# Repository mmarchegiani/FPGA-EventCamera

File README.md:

# FPGA-EventCamera
In the present work, a simplified model of an event camera is implemented, featuring a 3 $\times$ 3 matrix of photodiodes that are read out from a 12-channel ADC multiplexer in synchronous mode.

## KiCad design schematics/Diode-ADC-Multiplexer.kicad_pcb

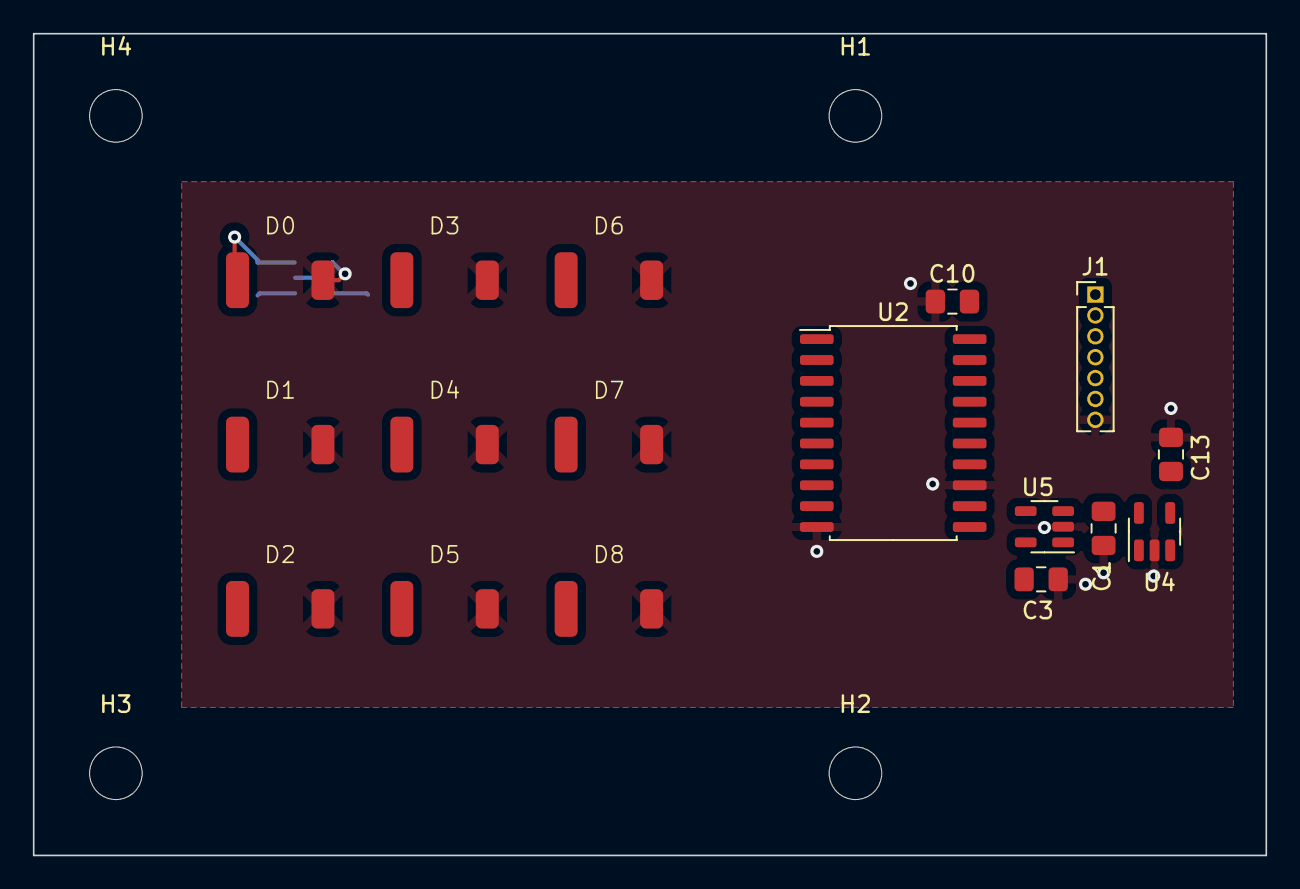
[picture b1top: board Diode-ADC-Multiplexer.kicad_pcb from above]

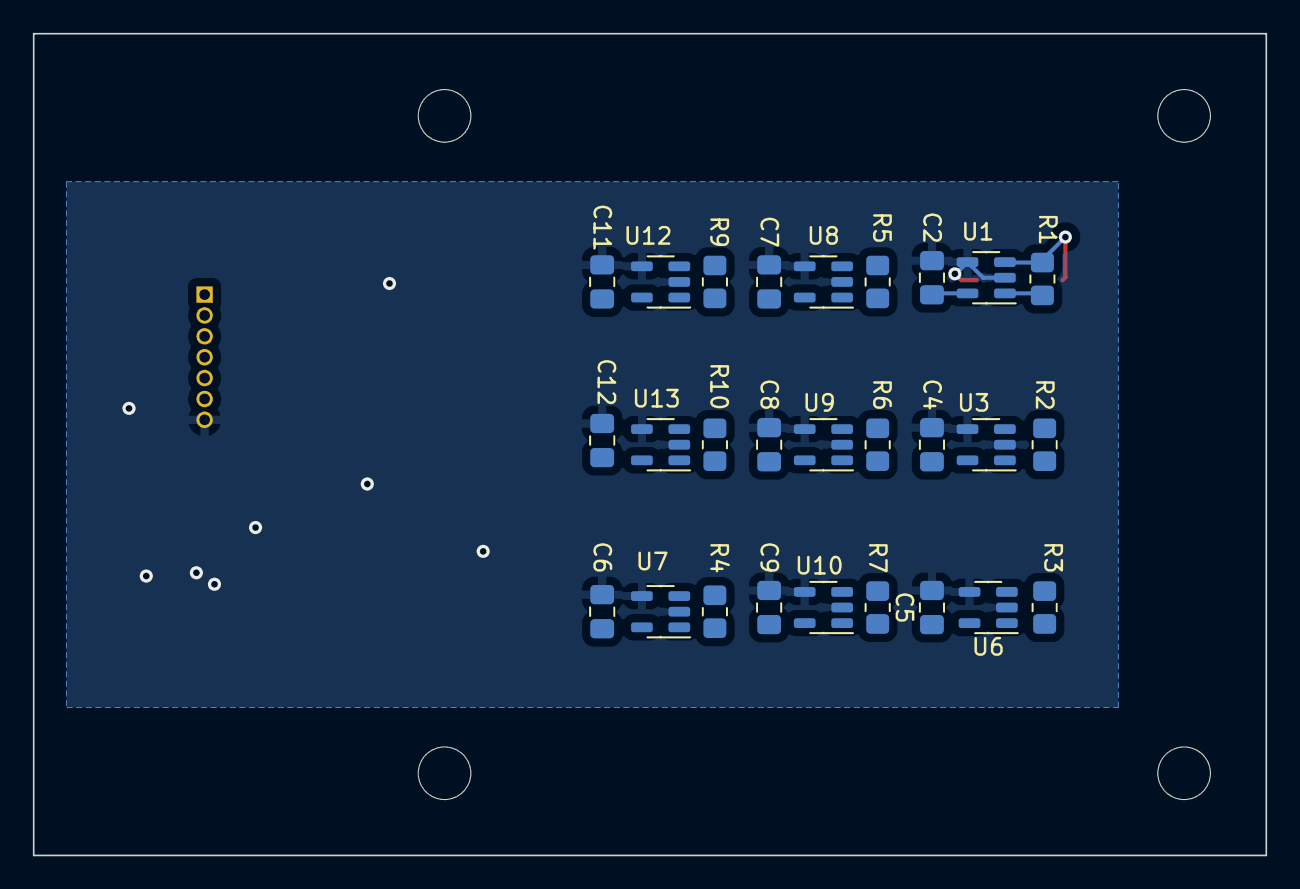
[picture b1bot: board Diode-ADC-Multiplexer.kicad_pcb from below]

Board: 2 copper layers, 75.0 x 50.0 mm, 48 parts (27 on the bottom side), 27 nets.

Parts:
C1: 22n; C_0805_2012Metric_Pad1.18x1.45mm_HandSolder
C2, C3, C4, C5, C6, C7, C8, C9, C10, C11, C12, C13: 100n; C_0805_2012Metric_Pad1.18x1.45mm_HandSolder
D0, D1, D2, D3, D4, D5, D6, D7, D8: SFH2240A01; Osram_SFH2240
H1, H2, H3, H4: MountingHole; MountingHole_3.2mm_M3
J1: To/From FPGA; PinHeader_1x07_P1.27mm_Vertical
R1, R2, R3, R4, R5, R6, R7, R9, R10: R; R_0805_2012Metric_Pad1.20x1.40mm_HandSolder
U1, U3, U5, U6, U7, U8, U9, U10, U12, U13: MCP601; SOT-23-5
U2: TLV2553; SOIC-20W_7.5x12.8mm_P1.27mm
U4: LM4120IM5-2.5; SOT-23-5

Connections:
+3.3V: C2.1, C3.1, C4.1, C5.1, C6.1, C7.1, C8.1, C9.1, C10.2, C11.1, C12.1, C13.1, J1.1, U1.5 (V+), U2.20 (VCC), U3.5 (V+), U4.3 (EN), U4.4 (VIN), U5.5 (V+), U6.5 (V+), U7.5 (V+), U8.5 (V+), U9.5 (V+), U10.5 (V+), U12.5 (V+), U13.5 (V+)
DATA_IN: J1.4, U2.17 (DATA_IN)
DATA_OUT: J1.3, U2.16 (DATA_OUT)
Diode_0: R1.2, U1.1, U2.1 (AIN0)
Diode_1: R2.2, U2.2 (AIN1), U3.1
Diode_2: R3.2, U2.3 (AIN2), U6.1
Diode_3: R5.2, U2.4 (AIN3), U8.1
Diode_4: R6.2, U2.5 (AIN4), U9.1
Diode_5: R7.2, U2.6 (AIN5), U10.1
Diode_6: R9.2, U2.7 (AIN6), U12.1
Diode_7: R10.2, U2.8 (AIN7), U13.1
Diode_8: R4.2, U2.9 (AIN8), U7.1
EOC: J1.2, U2.19 (EOC)
GND: C1.2, C2.2, C3.2, C4.2, C5.2, C6.2, C7.2, C8.2, C9.2, C10.1, C11.2, C12.2, C13.2, D0.2 (A), D1.2 (A), D2.2 (A), D3.2 (A), D4.2 (A), D5.2 (A), D6.2 (A), D7.2 (A), D8.2 (A), J1.7, U1.2 (V-), U1.4 (-), U2.10 (GND), U2.13 (REF-), U3.2 (V-), U3.4 (-), U4.2 (GND), U5.2 (V-), U6.2 (V-), U6.4 (-), U7.2 (V-), U7.4 (-), U8.2 (V-), U8.4 (-), U9.2 (V-), U9.4 (-), U10.2 (V-), U10.4 (-), U12.2 (V-), U12.4 (-), U13.2 (V-), U13.4 (-)
I/O_CLK: J1.6, U2.18 (I/O_CLOCK)
unnamed: D0.1 (K), R1.1, U1.3 (+)
unnamed: D1.1 (K), R2.1, U3.3 (+)
unnamed: D2.1 (K), R3.1, U6.3 (+)
unnamed: D3.1 (K), R5.1, U8.3 (+)
unnamed: D4.1 (K), R6.1, U9.3 (+)
unnamed: D5.1 (K), R7.1, U10.3 (+)
unnamed: D6.1 (K), R9.1, U12.3 (+)
unnamed: D7.1 (K), R10.1, U13.3 (+)
unnamed: D8.1 (K), R4.1, U7.3 (+)
unnamed: U2.14 (REF+), U5.1, U5.4 (-)
unnamed: C1.1, U4.5 (VREF), U5.3 (+)
~CS: J1.5, U2.15 (CS)

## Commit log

2023-05-17 Upload kicad schematics (wip)
